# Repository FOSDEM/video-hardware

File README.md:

# FOSDEM Video hardware

The FOSDEM video hardware project is about developing a 100% FOSS & open
hardware video streaming platform.

It is meant as a successor to the existing FOSDEM video boxes. These are
relatively bulky and expensive. We're aiming to build a cheap, compact and
lightweight device.

We hope to enable a shared platform with other conferences and projects.

## Status

We have confirmed the viability of the concept, and have produced a handful of
prototype boards. These boards enable us to work on the software stack first.
Once the software is in good shape, we will go back to the hardware drawing
board for the next version of the prototype. This next version will be built
using all the hardware components we are intending to use.

## Hardware
### Mainboard

We're evaluating the [Olimex A20-Olinuxino-Lime2](https://www.olimex.com/Products/OLinuXino/A20/A20-OLinuXino-LIME2/)
as the main board. It's well supported by the mainline linux kernel, thanks to
the efforts of the [linux-sunxi](https://linux-sunxi.org) community.

### HDMI input

The A20 does not have HDMI input. We're looking into building a custom HDMI
input board based upon the
[ADV7611](https://www.analog.com/en/products/adv7611.html). We push the hdmi to
the A20 over csi.

## Software

We plan to take in 720p60 hdmi audio & video. That is the most widely supported
resolution/refresh rate combination. It also hits a sweet spot between video
quality and complexity.

The hdmi input gets three destinations:
 * to the projector (with minimal delay!)
 * to the h264 encoder
 * to the lcd for live playback

The video encoding should be possible using the embedded cedrus vpu. The aac
audio encoding will have to be cpu based.

### Code

The current code can be found in the repositories below:

 * https://github.com/libv/fosdem-video-juggler
 * https://github.com/libv/sun4i-demp
 * https://github.com/libv/sun4i-csi1
 * https://github.com/libv/cedarx_h264_encoder
 * https://github.com/libv/fosdem-video-u-boot
 * https://github.com/libv/fosdem-video-linux

## Thanks

We would like to thank the [videobrick](https://videobrick.wordpress.com/)
[project](https://github.com/videobrick) for their inspiration.

A large part of this project is funded through the
[NGI0 PET Fund](https://nlnet.nl/PET/), a fund established by
[NLnet](https://nlnet.nl/) with financial support from the European Commission's
[Next Generation Internet](https://ngi.eu/) programme, under the aegis of DG
Communications Networks, Content and Technology under grant agreement No 825310.

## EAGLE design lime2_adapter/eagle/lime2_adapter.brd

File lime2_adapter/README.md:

# Breakout Board for the LIME2

Breakout board to test feasbility of the FOSDEM video hardware.

## Needed breakouts:
### FPC connector for CSI 1 to connect to Adafruit TFP401 board
### FPC LCD connector to connect to Banana PI LCD boards

## Wanted Breakouts:
### VGA Connector to breakout TVOUT

## Nice to have
### FPC connector to connect CSI0 to  Banana PI camera board

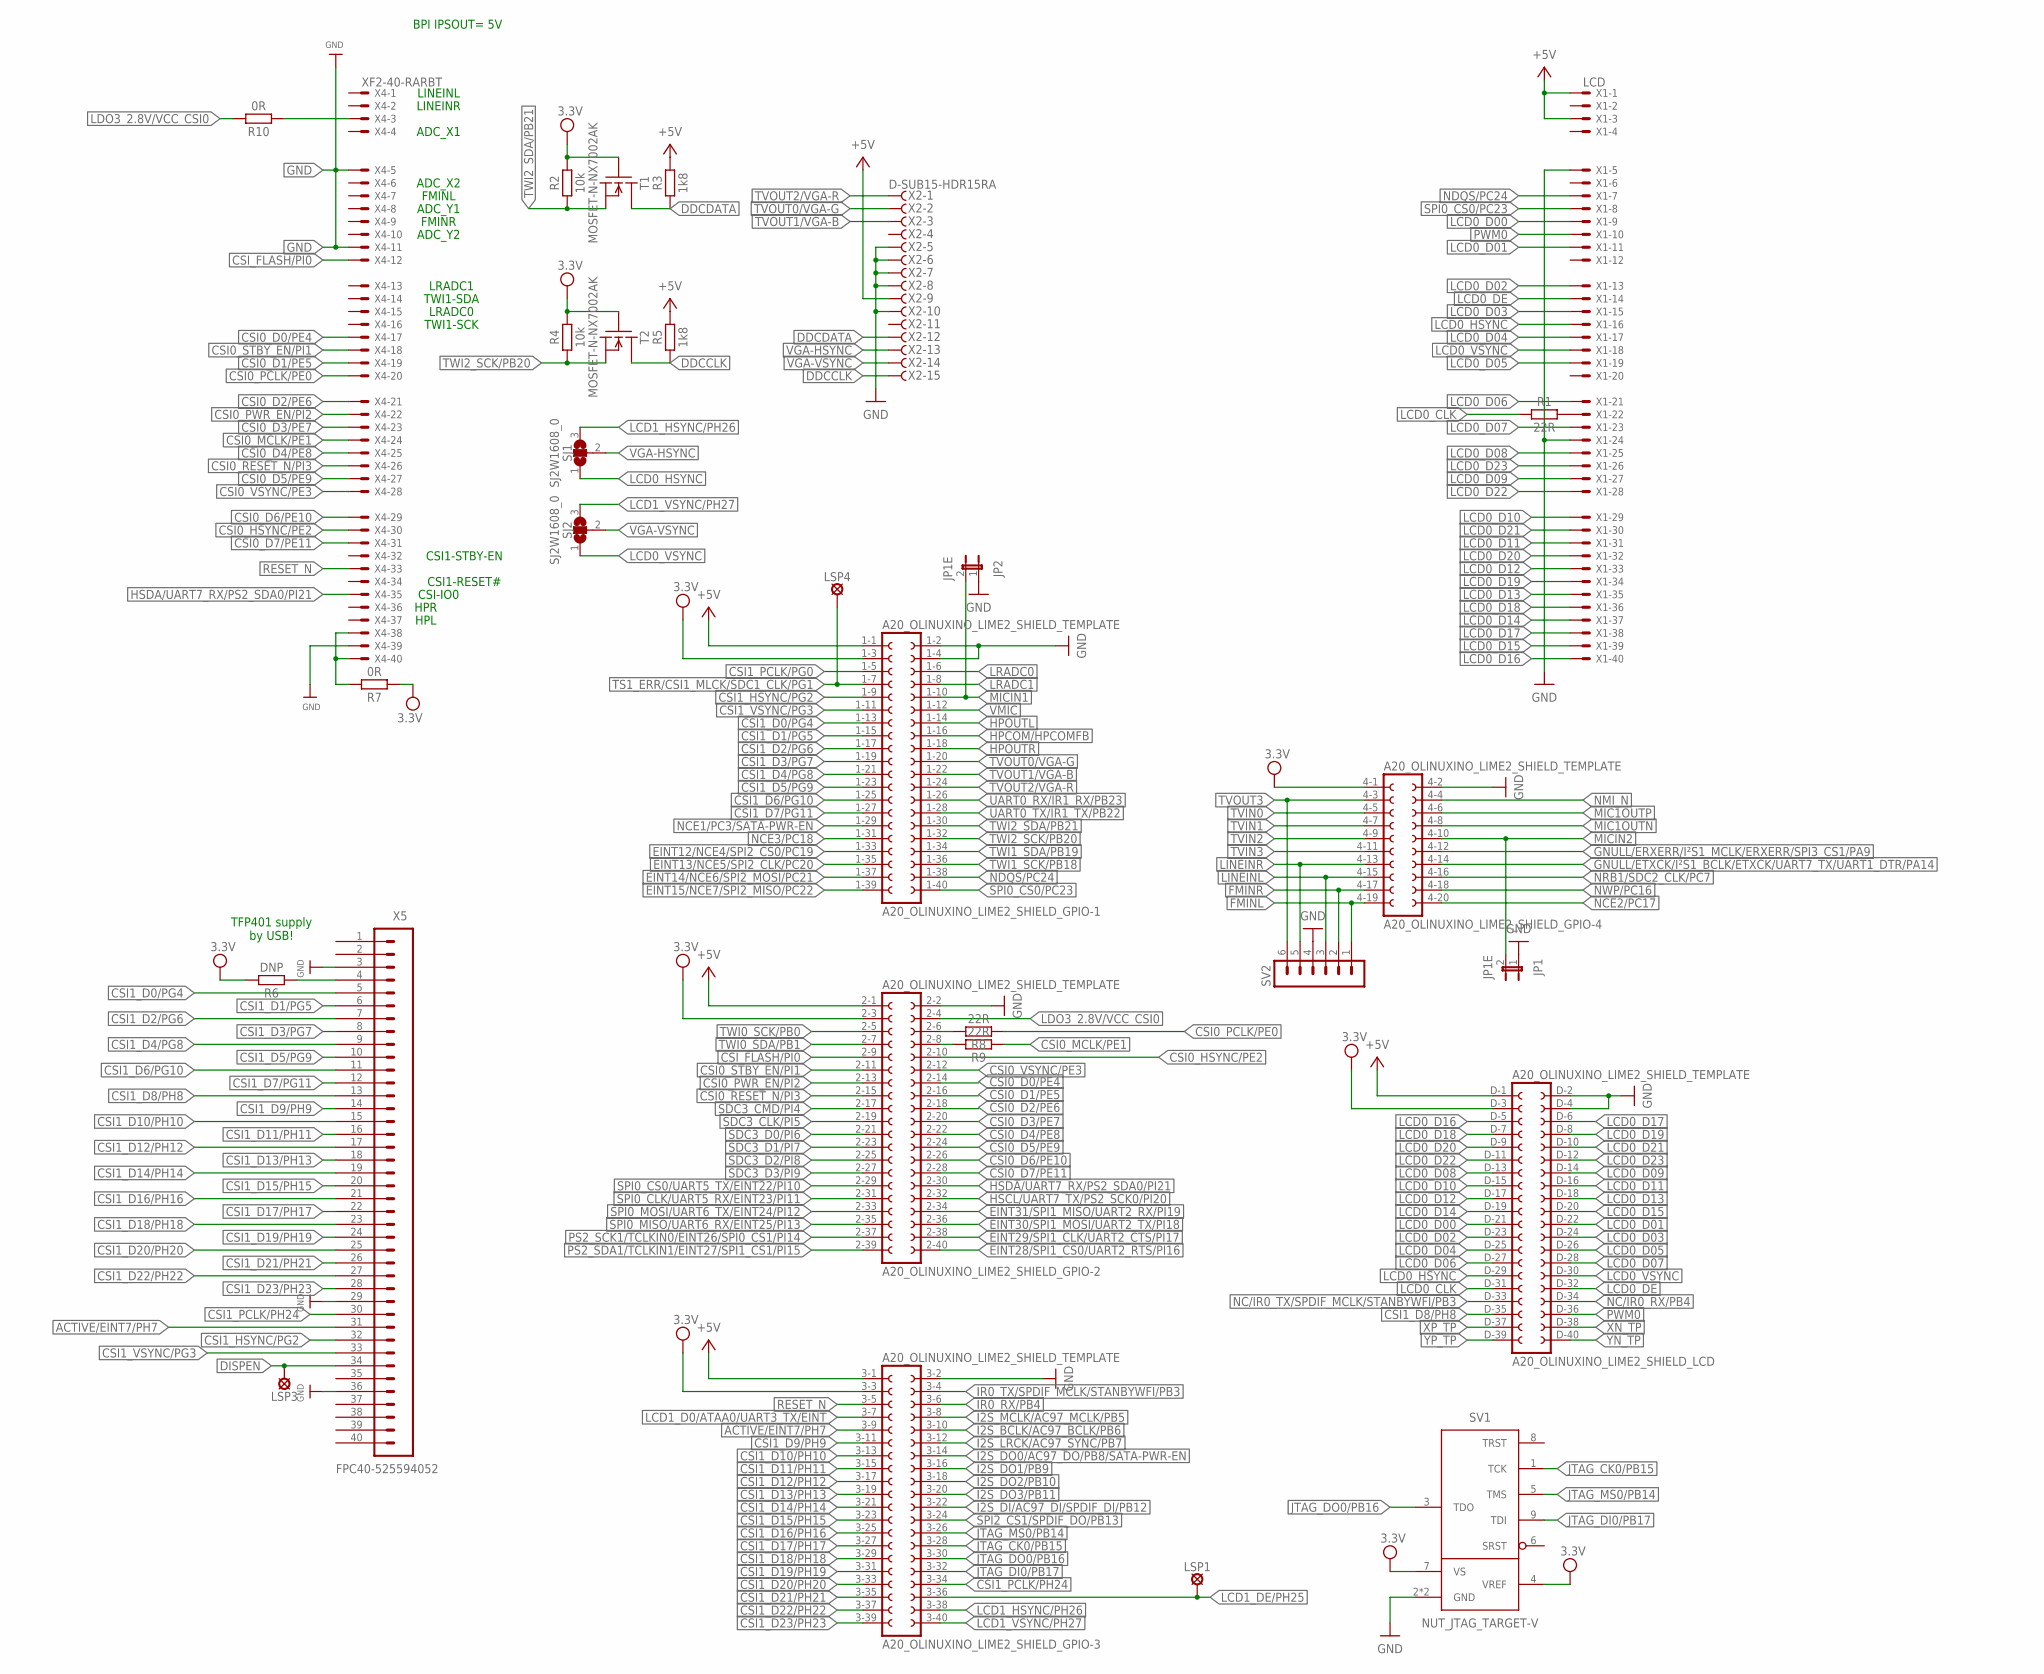
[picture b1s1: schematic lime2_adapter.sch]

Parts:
A20_OLINUXINO_LIME2_SHIELD: A20_OLINUXINO_LIME2_SHIELD_TEMPLATE; A20_OLINUXINO_LIME2_SHIELD
JP1, JP2: JP1E; JP1
LSP1, LSP3, LSP4: LSP-PAD15; PAD15
R1, R8, R9: 22R; RES1608X55N
R2, R4: 10k; RES1608X55N
R3, R5: 1k8; RES1608X55N
R6: DNP; RES1608X55N
R7, R10: 0R; RES1608X55N
SJ1, SJ2: SJ2W1608_0; SJ2_1608_0
SV1: NUT_JTAG_TARGET-V; ML10
SV2: MA06-1
T1, T2: MOSFET-N-NX7002AK; SOT95P230X110-3N
X1: LCD; 4-1734839-0
X2: D-SUB15-HDR15RA; HDR15RA
X4: XF2-40-RARBT; 4-1734839-0
X5: FPC40-525594052; 525594052

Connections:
+5V: A20_OLINUXINO_LIME2_SHIELD.1-1 (1), A20_OLINUXINO_LIME2_SHIELD.2-1 (1), A20_OLINUXINO_LIME2_SHIELD.3-1 (1), A20_OLINUXINO_LIME2_SHIELD.D-1 (1), R3.2, R5.2, X1.1 (MSV), X1.3 (MS), X2.9
ACTIVE/EINT7/PH7: A20_OLINUXINO_LIME2_SHIELD.3-9 (9), X5.31
CSI0_D0/PE4: A20_OLINUXINO_LIME2_SHIELD.2-14 (14), X4.17 (MS)
CSI0_D1/PE5: A20_OLINUXINO_LIME2_SHIELD.2-16 (16), X4.19 (MS)
CSI0_D2/PE6: A20_OLINUXINO_LIME2_SHIELD.2-18 (18), X4.21 (MS)
CSI0_D3/PE7: A20_OLINUXINO_LIME2_SHIELD.2-20 (20), X4.23 (MS)
CSI0_D4/PE8: A20_OLINUXINO_LIME2_SHIELD.2-22 (22), X4.25 (MS)
CSI0_D5/PE9: A20_OLINUXINO_LIME2_SHIELD.2-24 (24), X4.27 (MS)
CSI0_D6/PE10: A20_OLINUXINO_LIME2_SHIELD.2-26 (26), X4.29 (MS)
CSI0_D7/PE11: A20_OLINUXINO_LIME2_SHIELD.2-28 (28), X4.31 (MS)
CSI0_HSYNC/PE2: A20_OLINUXINO_LIME2_SHIELD.2-10 (10), X4.30 (MS)
CSI0_MCLK/PE1: R9.1, X4.24 (MS)
CSI0_PCLK/PE0: R8.1, X4.20 (MS)
CSI0_PWR_EN/PI2: A20_OLINUXINO_LIME2_SHIELD.2-13 (13), X4.22 (MS)
CSI0_RESET_N/PI3: A20_OLINUXINO_LIME2_SHIELD.2-15 (15), X4.26 (MS)
CSI0_STBY_EN/PI1: A20_OLINUXINO_LIME2_SHIELD.2-11 (11), X4.18 (MS)
CSI0_VSYNC/PE3: A20_OLINUXINO_LIME2_SHIELD.2-12 (12), X4.28 (MS)
CSI1_D0/PG4: A20_OLINUXINO_LIME2_SHIELD.1-13 (13), X5.5
CSI1_D1/PG5: A20_OLINUXINO_LIME2_SHIELD.1-15 (15), X5.6
CSI1_D2/PG6: A20_OLINUXINO_LIME2_SHIELD.1-17 (17), X5.7
CSI1_D3/PG7: A20_OLINUXINO_LIME2_SHIELD.1-19 (19), X5.8
CSI1_D4/PG8: A20_OLINUXINO_LIME2_SHIELD.1-21 (21), X5.9
CSI1_D5/PG9: A20_OLINUXINO_LIME2_SHIELD.1-23 (23), X5.10
CSI1_D6/PG10: A20_OLINUXINO_LIME2_SHIELD.1-25 (25), X5.11
CSI1_D7/PG11: A20_OLINUXINO_LIME2_SHIELD.1-27 (27), X5.12
CSI1_D8/PH8: A20_OLINUXINO_LIME2_SHIELD.D-35 (35), X5.13
CSI1_D9/PH9: A20_OLINUXINO_LIME2_SHIELD.3-11 (11), X5.14
CSI1_D10/PH10: A20_OLINUXINO_LIME2_SHIELD.3-13 (13), X5.15
CSI1_D11/PH11: A20_OLINUXINO_LIME2_SHIELD.3-15 (15), X5.16
CSI1_D12/PH12: A20_OLINUXINO_LIME2_SHIELD.3-17 (17), X5.17
CSI1_D13/PH13: A20_OLINUXINO_LIME2_SHIELD.3-19 (19), X5.18
CSI1_D14/PH14: A20_OLINUXINO_LIME2_SHIELD.3-21 (21), X5.19
CSI1_D15/PH15: A20_OLINUXINO_LIME2_SHIELD.3-23 (23), X5.20
CSI1_D16/PH16: A20_OLINUXINO_LIME2_SHIELD.3-25 (25), X5.21
CSI1_D17/PH17: A20_OLINUXINO_LIME2_SHIELD.3-27 (27), X5.22
CSI1_D18/PH18: A20_OLINUXINO_LIME2_SHIELD.3-29 (29), X5.23
CSI1_D19/PH19: A20_OLINUXINO_LIME2_SHIELD.3-31 (31), X5.24
CSI1_D20/PH20: A20_OLINUXINO_LIME2_SHIELD.3-33 (33), X5.25
CSI1_D21/PH21: A20_OLINUXINO_LIME2_SHIELD.3-35 (35), X5.26
CSI1_D22/PH22: A20_OLINUXINO_LIME2_SHIELD.3-37 (37), X5.27
CSI1_D23/PH23: A20_OLINUXINO_LIME2_SHIELD.3-39 (39), X5.28
CSI1_HSYNC/PG2: A20_OLINUXINO_LIME2_SHIELD.1-9 (9), X5.32
CSI1_PCLK/PG0: A20_OLINUXINO_LIME2_SHIELD.1-5 (5)
CSI1_PCLK/PH24: A20_OLINUXINO_LIME2_SHIELD.3-34 (34), X5.30
CSI1_VSYNC/PG3: A20_OLINUXINO_LIME2_SHIELD.1-11 (11), X5.33
CSI_FLASH/PI0: A20_OLINUXINO_LIME2_SHIELD.2-9 (9), X4.12 (MS)
DDCCLK: R5.1, T2.3 (D), X2.15
DDCDATA: R3.1, T1.3 (D), X2.12
DISPEN: LSP3.MP, X5.34
EINT12/NCE4/SPI2_CS0/PC19: A20_OLINUXINO_LIME2_SHIELD.1-33 (33)
EINT13/NCE5/SPI2_CLK/PC20: A20_OLINUXINO_LIME2_SHIELD.1-35 (35)
EINT14/NCE6/SPI2_MOSI/PC21: A20_OLINUXINO_LIME2_SHIELD.1-37 (37)
EINT15/NCE7/SPI2_MISO/PC22: A20_OLINUXINO_LIME2_SHIELD.1-39 (39)
EINT28/SPI1_CS0/UART2_RTS/PI16: A20_OLINUXINO_LIME2_SHIELD.2-40 (40)
EINT29/SPI1_CLK/UART2_CTS/PI17: A20_OLINUXINO_LIME2_SHIELD.2-38 (38)
EINT30/SPI1_MOSI/UART2_TX/PI18: A20_OLINUXINO_LIME2_SHIELD.2-36 (36)
EINT31/SPI1_MISO/UART2_RX/PI19: A20_OLINUXINO_LIME2_SHIELD.2-34 (34)
FMINL: A20_OLINUXINO_LIME2_SHIELD.4-19 (19), SV2.1
FMINR: A20_OLINUXINO_LIME2_SHIELD.4-17 (17), SV2.2
GND: A20_OLINUXINO_LIME2_SHIELD.1-2 (2), A20_OLINUXINO_LIME2_SHIELD.1-4 (4), A20_OLINUXINO_LIME2_SHIELD.2-2 (2), A20_OLINUXINO_LIME2_SHIELD.3-2 (2), A20_OLINUXINO_LIME2_SHIELD.4-2 (2), A20_OLINUXINO_LIME2_SHIELD.D-2 (2), A20_OLINUXINO_LIME2_SHIELD.D-4 (4), JP1.1, JP2.1, SV1.2 (GND), SV1.10 (GND), SV2.4, X1.5 (MS), X1.24 (MS), X2.5, X2.6, X2.7, X2.8, X2.10, X4.5 (MS), X4.11 (MS), X4.39 (MS), X5.3, X5.29, X5.36
GNULL/ERXERR/I²S1_MCLK/ERXERR/SPI3_CS1/PA9: A20_OLINUXINO_LIME2_SHIELD.4-12 (12)
GNULL/ETXCK/I²S1_BCLK/ETXCK/UART7_TX/UART1_DTR/PA14: A20_OLINUXINO_LIME2_SHIELD.4-14 (14)
HPCOM/HPCOMFB: A20_OLINUXINO_LIME2_SHIELD.1-16 (16)
HPOUTL: A20_OLINUXINO_LIME2_SHIELD.1-14 (14)
HPOUTR: A20_OLINUXINO_LIME2_SHIELD.1-18 (18)
HSCL/UART7_TX/PS2_SCK0/PI20: A20_OLINUXINO_LIME2_SHIELD.2-32 (32)
HSDA/UART7_RX/PS2_SDA0/PI21: A20_OLINUXINO_LIME2_SHIELD.2-30 (30), X4.35 (MS)
I2S_BCLK/AC97_BCLK/PB6: A20_OLINUXINO_LIME2_SHIELD.3-10 (10)
I2S_DI/AC97_DI/SPDIF_DI/PB12: A20_OLINUXINO_LIME2_SHIELD.3-22 (22)
I2S_DO0/AC97_DO/PB8/SATA-PWR-EN: A20_OLINUXINO_LIME2_SHIELD.3-14 (14)
I2S_DO1/PB9: A20_OLINUXINO_LIME2_SHIELD.3-16 (16)
I2S_DO2/PB10: A20_OLINUXINO_LIME2_SHIELD.3-18 (18)
I2S_DO3/PB11: A20_OLINUXINO_LIME2_SHIELD.3-20 (20)
I2S_LRCK/AC97_SYNC/PB7: A20_OLINUXINO_LIME2_SHIELD.3-12 (12)
I2S_MCLK/AC97_MCLK/PB5: A20_OLINUXINO_LIME2_SHIELD.3-8 (8)
IR0_RX/PB4: A20_OLINUXINO_LIME2_SHIELD.3-6 (6)
IR0_TX/SPDIF_MCLK/STANBYWFI/PB3: A20_OLINUXINO_LIME2_SHIELD.3-4 (4)
JTAG_CK0/PB15: A20_OLINUXINO_LIME2_SHIELD.3-28 (28), SV1.1 (TCK)
JTAG_DI0/PB17: A20_OLINUXINO_LIME2_SHIELD.3-32 (32), SV1.9 (TDI)
JTAG_DO0/PB16: A20_OLINUXINO_LIME2_SHIELD.3-30 (30), SV1.3 (TDO)
JTAG_MS0/PB14: A20_OLINUXINO_LIME2_SHIELD.3-26 (26), SV1.5 (TMS)
LCD0_CLK: A20_OLINUXINO_LIME2_SHIELD.D-31 (31), R1.1
LCD0_CLKR: R1.2, X1.22 (MS)
LCD0_D00: A20_OLINUXINO_LIME2_SHIELD.D-21 (21), X1.9 (MS)
LCD0_D01: A20_OLINUXINO_LIME2_SHIELD.D-22 (22), X1.11 (MS)
LCD0_D02: A20_OLINUXINO_LIME2_SHIELD.D-23 (23), X1.13 (MS)
LCD0_D03: A20_OLINUXINO_LIME2_SHIELD.D-24 (24), X1.15 (MS)
LCD0_D04: A20_OLINUXINO_LIME2_SHIELD.D-25 (25), X1.17 (MS)
LCD0_D05: A20_OLINUXINO_LIME2_SHIELD.D-26 (26), X1.19 (MS)
LCD0_D06: A20_OLINUXINO_LIME2_SHIELD.D-27 (27), X1.21 (MS)
LCD0_D07: A20_OLINUXINO_LIME2_SHIELD.D-28 (28), X1.23 (MS)
LCD0_D08: A20_OLINUXINO_LIME2_SHIELD.D-13 (13), X1.25 (MS)
LCD0_D09: A20_OLINUXINO_LIME2_SHIELD.D-14 (14), X1.27 (MS)
LCD0_D10: A20_OLINUXINO_LIME2_SHIELD.D-15 (15), X1.29 (MS)
LCD0_D11: A20_OLINUXINO_LIME2_SHIELD.D-16 (16), X1.31 (MS)
LCD0_D12: A20_OLINUXINO_LIME2_SHIELD.D-17 (17), X1.33 (MS)
LCD0_D13: A20_OLINUXINO_LIME2_SHIELD.D-18 (18), X1.35 (MS)
LCD0_D14: A20_OLINUXINO_LIME2_SHIELD.D-19 (19), X1.37 (MS)
LCD0_D15: A20_OLINUXINO_LIME2_SHIELD.D-20 (20), X1.39 (MS)
LCD0_D16: A20_OLINUXINO_LIME2_SHIELD.D-5 (5), X1.40 (MS)
LCD0_D17: A20_OLINUXINO_LIME2_SHIELD.D-6 (6), X1.38 (MS)
LCD0_D18: A20_OLINUXINO_LIME2_SHIELD.D-7 (7), X1.36 (MS)
LCD0_D19: A20_OLINUXINO_LIME2_SHIELD.D-8 (8), X1.34 (MS)
LCD0_D20: A20_OLINUXINO_LIME2_SHIELD.D-9 (9), X1.32 (MS)
LCD0_D21: A20_OLINUXINO_LIME2_SHIELD.D-10 (10), X1.30 (MS)
LCD0_D22: A20_OLINUXINO_LIME2_SHIELD.D-11 (11), X1.28 (MS)
LCD0_D23: A20_OLINUXINO_LIME2_SHIELD.D-12 (12), X1.26 (MS)
LCD0_DE: A20_OLINUXINO_LIME2_SHIELD.D-32 (32), X1.14 (MS)
LCD0_HSYNC: A20_OLINUXINO_LIME2_SHIELD.D-29 (29), SJ1.1, X1.16 (MS)
LCD0_VSYNC: A20_OLINUXINO_LIME2_SHIELD.D-30 (30), SJ2.1, X1.18 (MS)
LCD1_D0/ATAA0/UART3_TX/EINT: A20_OLINUXINO_LIME2_SHIELD.3-7 (7)
LCD1_DE/PH25: A20_OLINUXINO_LIME2_SHIELD.3-36 (36), LSP1.MP
LCD1_HSYNC/PH26: A20_OLINUXINO_LIME2_SHIELD.3-38 (38), SJ1.3
LCD1_VSYNC/PH27: A20_OLINUXINO_LIME2_SHIELD.3-40 (40), SJ2.3
LDO3_2.8V/VCC_CSI0: A20_OLINUXINO_LIME2_SHIELD.2-4 (4), R10.2
LINEINL: A20_OLINUXINO_LIME2_SHIELD.4-15 (15), SV2.3
LINEINR: A20_OLINUXINO_LIME2_SHIELD.4-13 (13), SV2.5
LRADC0: A20_OLINUXINO_LIME2_SHIELD.1-6 (6)
LRADC1: A20_OLINUXINO_LIME2_SHIELD.1-8 (8)
MIC1OUTN: A20_OLINUXINO_LIME2_SHIELD.4-8 (8)
MIC1OUTP: A20_OLINUXINO_LIME2_SHIELD.4-6 (6)
MICIN1: A20_OLINUXINO_LIME2_SHIELD.1-10 (10), JP2.2
MICIN2: A20_OLINUXINO_LIME2_SHIELD.4-10 (10), JP1.2
unnamed: R6.1, X5.4
unnamed: R7.2, X4.38 (MS), X4.40 (MS)
unnamed: R10.1, X4.3 (MS)
unnamed: A20_OLINUXINO_LIME2_SHIELD.2-6 (6), R8.2
unnamed: A20_OLINUXINO_LIME2_SHIELD.2-8 (8), R9.2
NC/IR0_RX/PB4: A20_OLINUXINO_LIME2_SHIELD.D-34 (34)
NC/IR0_TX/SPDIF_MCLK/STANBYWFI/PB3: A20_OLINUXINO_LIME2_SHIELD.D-33 (33)
NCE1/PC3/SATA-PWR-EN: A20_OLINUXINO_LIME2_SHIELD.1-29 (29)
NCE2/PC17: A20_OLINUXINO_LIME2_SHIELD.4-20 (20)
NCE3/PC18: A20_OLINUXINO_LIME2_SHIELD.1-31 (31)
NDQS/PC24: A20_OLINUXINO_LIME2_SHIELD.1-38 (38), X1.7 (MS)
NMI_N: A20_OLINUXINO_LIME2_SHIELD.4-4 (4)
NRB1/SDC2_CLK/PC7: A20_OLINUXINO_LIME2_SHIELD.4-16 (16)
NWP/PC16: A20_OLINUXINO_LIME2_SHIELD.4-18 (18)
PS2_SCK1/TCLKIN0/EINT26/SPI0_CS1/PI14: A20_OLINUXINO_LIME2_SHIELD.2-37 (37)
PS2_SDA1/TCLKIN1/EINT27/SPI1_CS1/PI15: A20_OLINUXINO_LIME2_SHIELD.2-39 (39)
PWM0: A20_OLINUXINO_LIME2_SHIELD.D-36 (36), X1.10 (MS)
RESET_N: A20_OLINUXINO_LIME2_SHIELD.3-5 (5), X4.33 (MS)
SDC3_CLK/PI5: A20_OLINUXINO_LIME2_SHIELD.2-19 (19)
SDC3_CMD/PI4: A20_OLINUXINO_LIME2_SHIELD.2-17 (17)
SDC3_D0/PI6: A20_OLINUXINO_LIME2_SHIELD.2-21 (21)
SDC3_D1/PI7: A20_OLINUXINO_LIME2_SHIELD.2-23 (23)
SDC3_D2/PI8: A20_OLINUXINO_LIME2_SHIELD.2-25 (25)
SDC3_D3/PI9: A20_OLINUXINO_LIME2_SHIELD.2-27 (27)
SPI0_CLK/UART5_RX/EINT23/PI11: A20_OLINUXINO_LIME2_SHIELD.2-31 (31)
SPI0_CS0/PC23: A20_OLINUXINO_LIME2_SHIELD.1-40 (40), X1.8 (MS)
SPI0_CS0/UART5_TX/EINT22/PI10: A20_OLINUXINO_LIME2_SHIELD.2-29 (29)
SPI0_MISO/UART6_RX/EINT25/PI13: A20_OLINUXINO_LIME2_SHIELD.2-35 (35)
SPI0_MOSI/UART6_TX/EINT24/PI12: A20_OLINUXINO_LIME2_SHIELD.2-33 (33)
SPI2_CS1/SPDIF_DO/PB13: A20_OLINUXINO_LIME2_SHIELD.3-24 (24)
TS1_ERR/CSI1_MLCK/SDC1_CLK/PG1: A20_OLINUXINO_LIME2_SHIELD.1-7 (7), LSP4.MP
TVIN0: A20_OLINUXINO_LIME2_SHIELD.4-5 (5)
TVIN1: A20_OLINUXINO_LIME2_SHIELD.4-7 (7)
TVIN2: A20_OLINUXINO_LIME2_SHIELD.4-9 (9)
TVIN3: A20_OLINUXINO_LIME2_SHIELD.4-11 (11)
TVOUT0/VGA-G: A20_OLINUXINO_LIME2_SHIELD.1-20 (20), X2.2
TVOUT1/VGA-B: A20_OLINUXINO_LIME2_SHIELD.1-22 (22), X2.3
TVOUT2/VGA-R: A20_OLINUXINO_LIME2_SHIELD.1-24 (24), X2.1
TVOUT3: A20_OLINUXINO_LIME2_SHIELD.4-3 (3), SV2.6
TWI0_SCK/PB0: A20_OLINUXINO_LIME2_SHIELD.2-5 (5)
TWI0_SDA/PB1: A20_OLINUXINO_LIME2_SHIELD.2-7 (7)
TWI1_SCK/PB18: A20_OLINUXINO_LIME2_SHIELD.1-36 (36)
TWI1_SDA/PB19: A20_OLINUXINO_LIME2_SHIELD.1-34 (34)
TWI2_SCK/PB20: A20_OLINUXINO_LIME2_SHIELD.1-32 (32), R4.1, T2.2 (S)
TWI2_SDA/PB21: A20_OLINUXINO_LIME2_SHIELD.1-30 (30), R2.1, T1.2 (S)
UART0_RX/IR1_RX/PB23: A20_OLINUXINO_LIME2_SHIELD.1-26 (26)
UART0_TX/IR1_TX/PB22: A20_OLINUXINO_LIME2_SHIELD.1-28 (28)
VCC: A20_OLINUXINO_LIME2_SHIELD.1-3 (3), A20_OLINUXINO_LIME2_SHIELD.2-3 (3), A20_OLINUXINO_LIME2_SHIELD.3-3 (3), A20_OLINUXINO_LIME2_SHIELD.4-1 (1), A20_OLINUXINO_LIME2_SHIELD.D-3 (3), R2.2, R4.2, R6.2, R7.1, SV1.4 (VREF), SV1.7 (VS), T1.1 (G), T2.1 (G)
VGA-HSYNC: SJ1.2, X2.13
VGA-VSYNC: SJ2.2, X2.14
VMIC: A20_OLINUXINO_LIME2_SHIELD.1-12 (12)
XN_TP: A20_OLINUXINO_LIME2_SHIELD.D-38 (38)
XP_TP: A20_OLINUXINO_LIME2_SHIELD.D-37 (37)
YN_TP: A20_OLINUXINO_LIME2_SHIELD.D-40 (40)
YP_TP: A20_OLINUXINO_LIME2_SHIELD.D-39 (39)

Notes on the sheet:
TFP401 supply by USB!
BPI IPSOUT= 5V
CSI-IO0
HPL
HPR
CSI1-RESET#
CSI1-STBY-EN
TWI1-SCK
TWI1-SDA
LRADC0
LRADC1
FMINR
FMINL
ADC_X1
ADC_X2
ADC_Y1
ADC_Y2
LINEINR
LINEINL

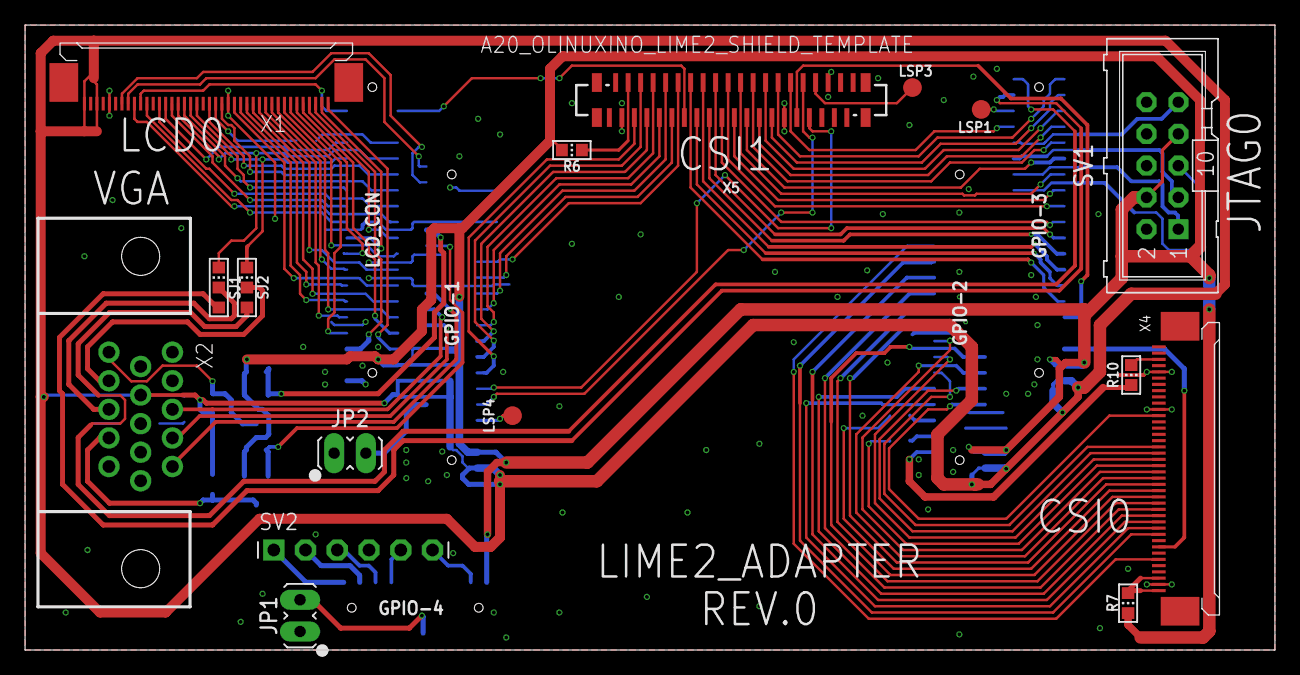
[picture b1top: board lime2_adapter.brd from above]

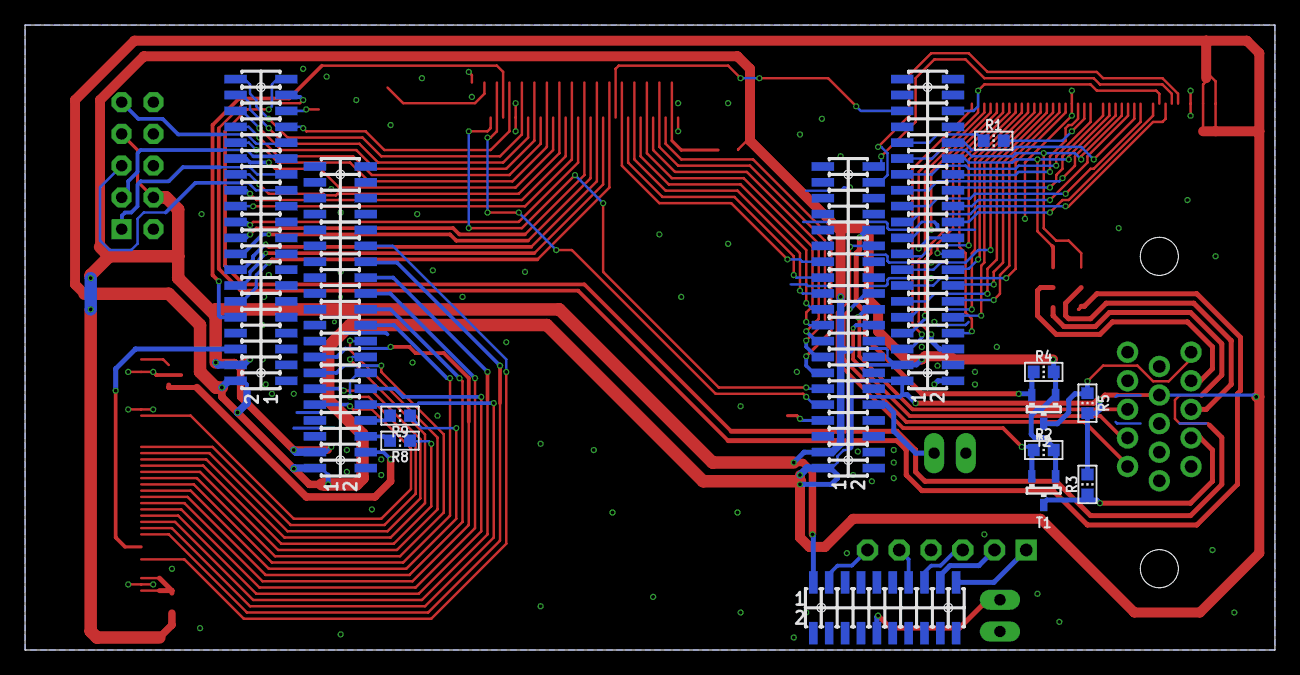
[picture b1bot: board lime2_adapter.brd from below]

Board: 2 copper layers, 100.0 x 50.0 mm, 26 parts (9 on the bottom side), 112 nets.

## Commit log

2019-05-06 Very rough illustration of a potential case design
    This is very quick and dirty, but it gets the idea across. We don't have
    all the measurements yet, so everything is very approximate.
2019-05-09 Add lime2-adapter: Breakout board for Lime2
    - FPC connections still under review
    - FPC CSI1/TFP401 connector changed to vertical type to avoid collision with
    ETH/USB block
2019-05-09 Realize ECOs from Luc 190508
    - Change X1-02 (X1B) to be disconnected
    - Change X1-04 (X1D) to be disconnected
    - Change X1-06 (X1F) to be disconnected
    - Change X1-07 (X1G) to GPIO1-38(PC24)
    - Change X1-08 (X1H) to GPIO1-40(PC23)
    - Change X1-12 (X1L) to be disconnected
2019-05-09 lime2_adapter
    - Change VCC_CSI0 (Camera) from X4-2 to X4-3
    - Connect X1-2 to GND.
    - Provide access to TVOUT3, LINEIN[L|R] and FMIN[L|R]
    - Provide access to MIC[1|2]
2019-05-09 lime2_adapter: Move LCD connector left to avoid collision with USB/ETH.
2019-05-13 case: sketch of a potential extrusion profile
2021-01-21 README: add status; link to software; thanks to NLnet

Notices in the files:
parts and their libraries:
microbuilder: This work is placed in the public domain, and may be freely used for commercial and non-commercial work with the following conditions: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
